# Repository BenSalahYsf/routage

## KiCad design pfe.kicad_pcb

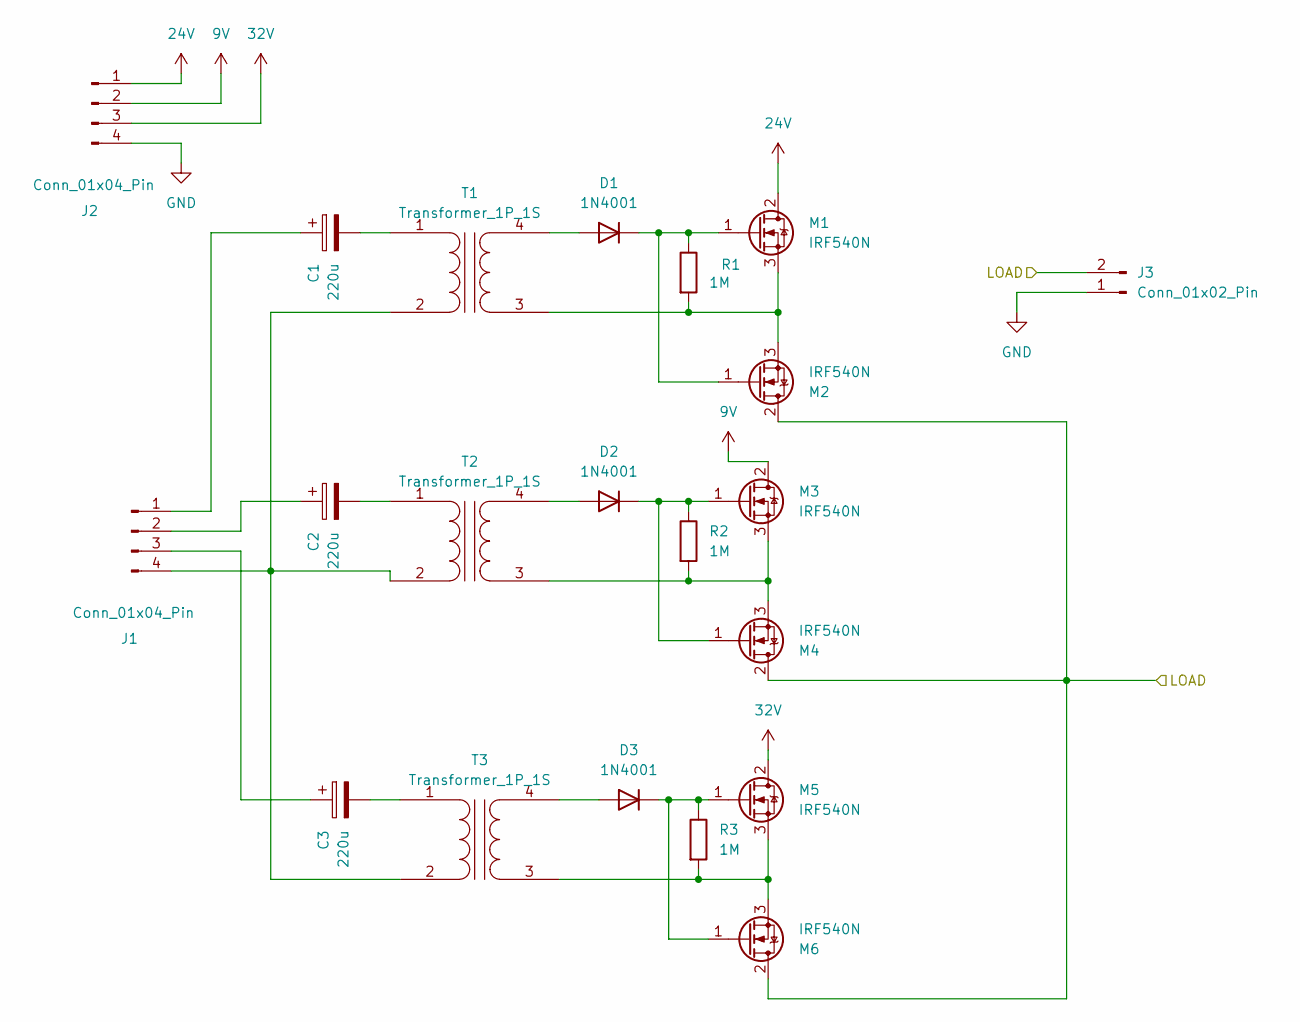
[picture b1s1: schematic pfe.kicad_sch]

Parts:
C1, C2, C3: 220u; CP_Radial_D6.3mm_P2.50mm
D1, D2, D3: 1N4001; D_DO-41_SOD81_P10.16mm_Horizontal
J1, J2: Conn_01x04_Pin; PinHeader_1x04_P2.54mm_Vertical
J3: Conn_01x02_Pin; PinHeader_1x02_P2.54mm_Vertical
M1, M2, M3, M4, M5, M6: IRF540N; TO-247-3_Vertical
R1, R2, R3: 1M; R_Axial_DIN0207_L6.3mm_D2.5mm_P10.16mm_Horizontal
T1, T2, T3: Transformer_1P_1S; Transformer_Toroid_Horizontal_D9.0mm_Amidon-T30

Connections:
9V: J2.2, M3.2 (D)
24V: J2.1, M1.2 (D)
32V: J2.3, M5.2 (D)
/LOAD: J3.2, M2.2 (D), M4.2 (D), M6.2 (D)
GND: J2.4, J3.1
unnamed: D1.2 (A), T1.4 (SB)
unnamed: D1.1 (K), M1.1 (G), M2.1 (G), R1.1
unnamed: D2.2 (A), T2.4 (SB)
unnamed: D2.1 (K), M3.1 (G), M4.1 (G), R2.1
unnamed: D3.2 (A), T3.4 (SB)
unnamed: D3.1 (K), M5.1 (G), M6.1 (G), R3.1
unnamed: C1.1, J1.1
unnamed: C2.1, J1.2
unnamed: C3.1, J1.3
unnamed: J1.4, T1.2 (AB), T2.2 (AB), T3.2 (AB)
unnamed: M1.3 (S), M2.3 (S), R1.2, T1.3 (SA)
unnamed: M3.3 (S), M4.3 (S), R2.2, T2.3 (SA)
unnamed: M5.3 (S), M6.3 (S), R3.2, T3.3 (SA)
unnamed: C1.2, T1.1 (AA)
unnamed: C2.2, T2.1 (AA)
unnamed: C3.2, T3.1 (AA)

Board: 2 copper layers, 21 parts (0 on the bottom side), 21 nets, no tracks yet.
